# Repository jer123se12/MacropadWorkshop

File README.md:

# Macropad Workshop
These are the files to be used in conjunction with the macropad workshop. all software files can be found under /firmware and all hardware design files can be found under hardware

This is a 3 key macropad powered either by *QMK+VIAL* or *CIRCUITPYTHON*.

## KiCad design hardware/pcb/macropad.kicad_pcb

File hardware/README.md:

# Hardware for macropad

Designs are using onshape with the link [here](https://cad.onshape.com/documents/d9cd8b63baf7e8b94c16fb3d/w/25324f1a9aba75b8554a8c8d/e/e8deb201892b484adec0b776).

PCB designs can be found under `pcb/` and the lazercutting files can be found under `lazercut/`

# Additional Hardware
To build this, you also need other parts

|Part |Qty|
|:---|:---:|
|m2x6 screw| 4|
|m2x8 standoff|4|
|any compatible Cherry switch |3|
|waveshare RP2040 zero|1|

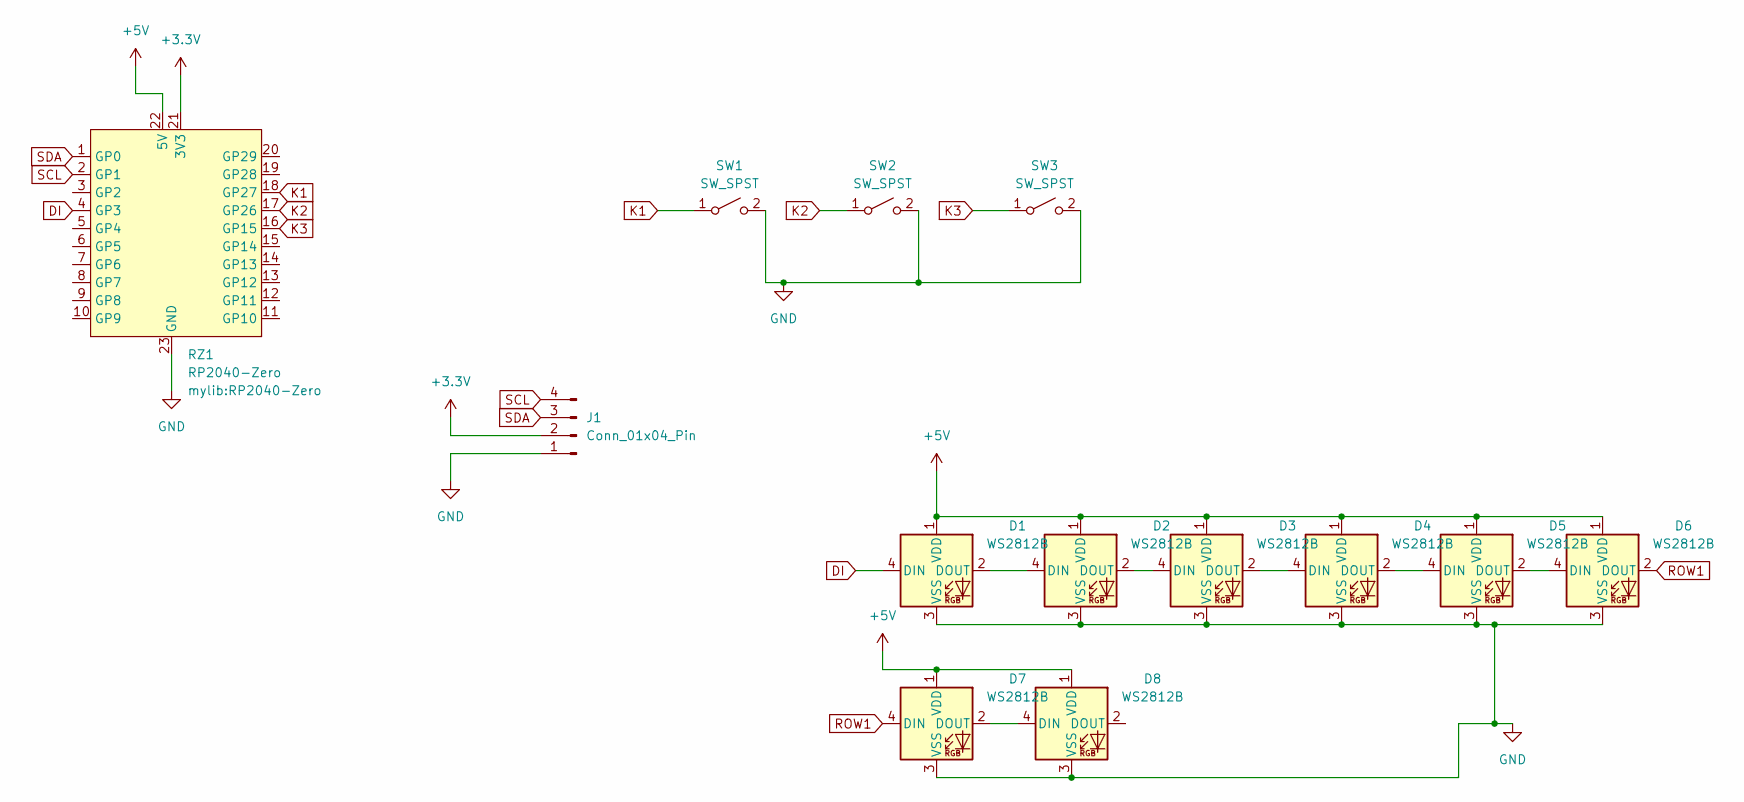
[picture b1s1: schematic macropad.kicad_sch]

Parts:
D1, D2, D3, D4, D5, D6, D7, D8: WS2812B; new led
J1: Conn_01x04_Pin; FanPinHeader_1x04_P2.54mm_Vertical
RZ1: RP2040-Zero
SW1, SW2, SW3: SW_SPST; SW_Cherry_MX_1.00u_PCB

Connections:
+3.3V: J1.2, RZ1.21 (3V3)
+5V: D1.1 (VDD), D2.1 (VDD), D3.1 (VDD), D4.1 (VDD), D5.1 (VDD), D6.1 (VDD), D7.1 (VDD), D8.1 (VDD), RZ1.22 (5V)
DI: D1.4 (DIN), RZ1.4 (GP3)
GND: D1.3 (VSS), D2.3 (VSS), D3.3 (VSS), D4.3 (VSS), D5.3 (VSS), D6.3 (VSS), D7.3 (VSS), D8.3 (VSS), J1.1, RZ1.23 (GND), SW1.2 (B), SW2.2 (B), SW3.2 (B)
K1: RZ1.18 (GP27), SW1.1 (A)
K2: RZ1.17 (GP26), SW2.1 (A)
K3: RZ1.16 (GP15), SW3.1 (A)
unnamed: D1.2 (DOUT), D2.4 (DIN)
unnamed: D2.2 (DOUT), D3.4 (DIN)
unnamed: D3.2 (DOUT), D4.4 (DIN)
unnamed: D4.2 (DOUT), D5.4 (DIN)
unnamed: D5.2 (DOUT), D6.4 (DIN)
unnamed: D7.2 (DOUT), D8.4 (DIN)
ROW1: D6.2 (DOUT), D7.4 (DIN)
SCL: J1.4, RZ1.2 (GP1)
SDA: J1.3, RZ1.1 (GP0)

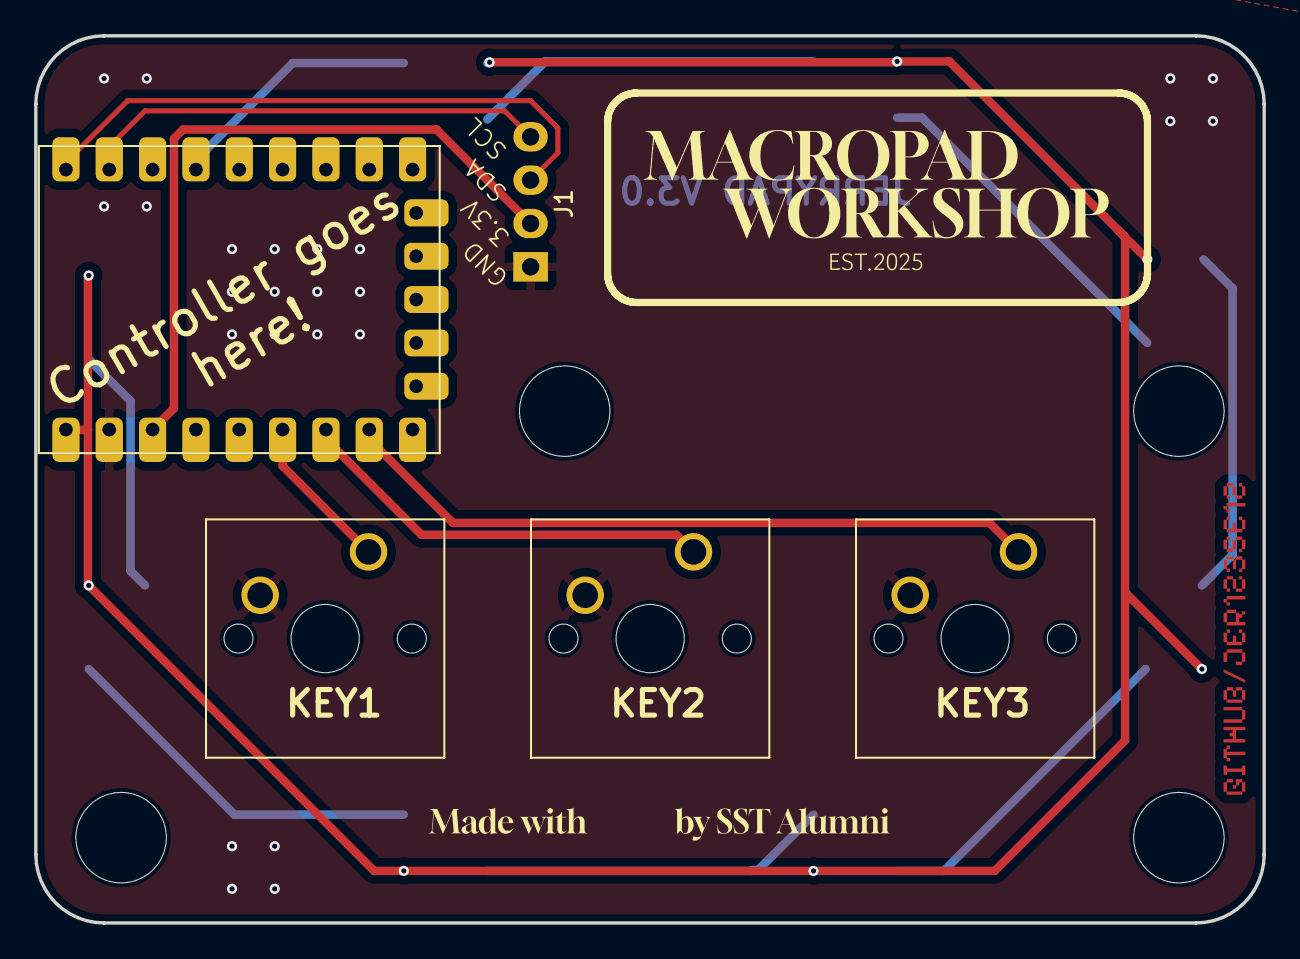
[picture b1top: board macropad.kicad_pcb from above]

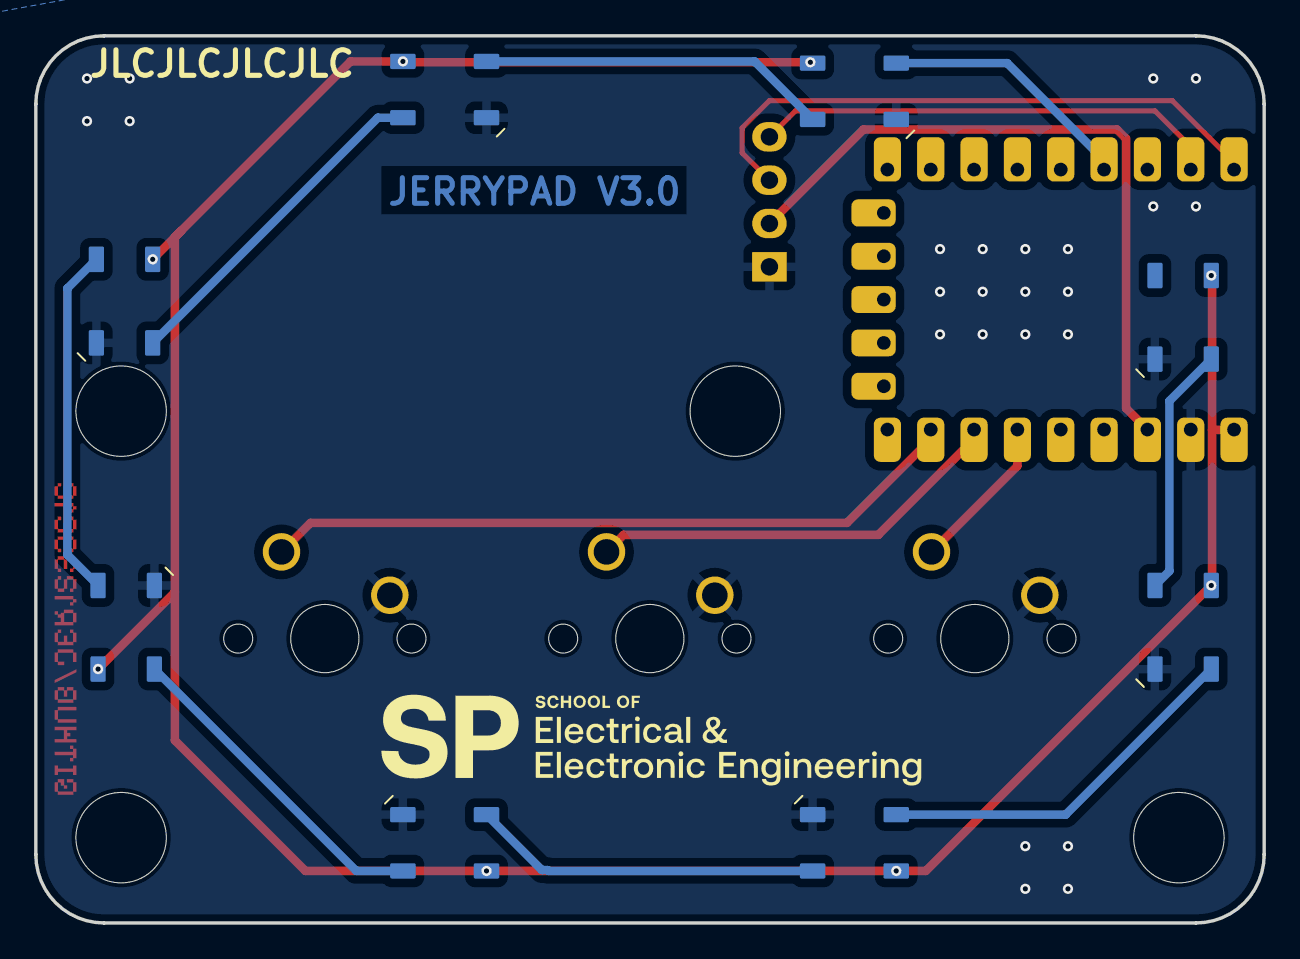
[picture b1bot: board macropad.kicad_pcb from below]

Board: 2 copper layers, 72.0 x 52.0 mm, 13 parts (8 on the bottom side), 16 nets.

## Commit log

2025-03-09 added readme
2025-03-09 added everything
2025-03-16 added code im going to use
2025-03-16 swapped the braces oops
